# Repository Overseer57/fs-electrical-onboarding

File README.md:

# FS Electrical Onboarding

This git repository contains onboarding projects for each electrical subsystem:

- Low Voltage (LV)
- Power Electronics (PE)
- Firmware (FW)

You must complete one onboarding project to be able to join the team. Our goal
is to get to know you and how you work, not to grade your skills or abilities
coming in. We want to see that you're excited and willing to learn, not that you
know everything already! To make team roster selection easier for us, you'll
only officially be assigned to one specific subsystem within the Electrical
team. But once you've joined, you're encouraged to contribute and participate in
as many ways as you're excited to and have bandwidth for.

**Read the README file in each subsystem's folder in this repo to get started on
the onboarding project for that subsystem.** You are encouraged to attempt
whichever of the three onboarding projects that you find interesting!

---

Note: Clone this repository recursively (`git clone --recursive`). If you
didn't, be sure to initialize the submodule: `git submodule init` _and_ `git
submodule update`

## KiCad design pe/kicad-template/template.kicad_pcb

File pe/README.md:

**Formula Slug Power Electronics Onboarding**

Welcome to Formula Slug's Power Eletronics onboarding project! Refer to this
Google Doc for all information regarding this project:

[View the FS Power Electronics Onboarding Guide 26-27](https://docs.google.com/document/d/1htf_bj8dCnWR_2gC1TFTzJU0MFP1d0OxF1IBO_kqalM/edit?usp=sharing)

---

Note: Clone this repository recursively (`git clone --recursive`). If you
didn't, be sure to initialize the submodule: `git submodule init` _and_ `git
submodule update`

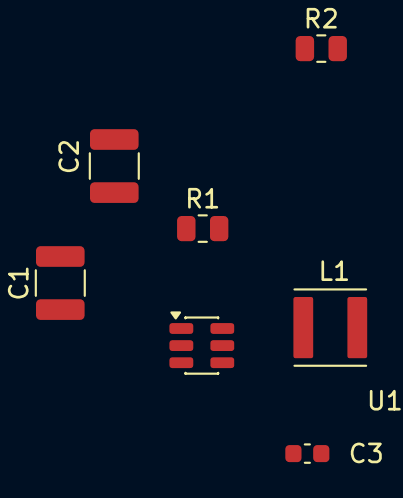
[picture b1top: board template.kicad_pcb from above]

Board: 2 copper layers, 7 parts (0 on the bottom side), 6 nets, no tracks yet.

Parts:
C1: 47uF; C_1210_3225Metric
C2: 10uF; C_1210_3225Metric
C3: 0.1uF; C_0603_1608Metric
L1: 4.7uH; L_Abracon_ASPI-4030S
R1: 54.9k; R_0805_2012Metric
R2: 10k; R_0805_2012Metric
U1: TPS562200; SOT-23-6

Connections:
+12V: C2.1, U1.3 (VIN), U1.5 (EN)
/VOUT: C1.1, L1.2, R1.2
GND: C1.2, C2.2, R2.2, U1.1 (GND)
unnamed: C3.1, L1.1, U1.2 (SW)
unnamed: C3.2, U1.6 (VBST)
unnamed: R1.1, R2.1, U1.4 (VFB)
